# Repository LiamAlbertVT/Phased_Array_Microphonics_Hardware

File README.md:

## Recent Updates

- Corrected the 48 V phantom-power wiring on all four XLR microphone inputs and added a filter before each delay chip.
- Reduced open PCB connections from 64 to 11. All 11 are in the power section.

## TODO (Upcoming Commits)

- Review the Q6 gate drive and the pin assignments on regulators U16 and U18 before finishing the power routing.

## Future Plans

- Test the Raspberry Pi Pico's delay clocks and its connection to the ADC.
  - Add Pico sample code in an `embedded/` directory.
- Build one microphone channel on a breadboard and check its gain, filter response, and delay before ordering the PCB.

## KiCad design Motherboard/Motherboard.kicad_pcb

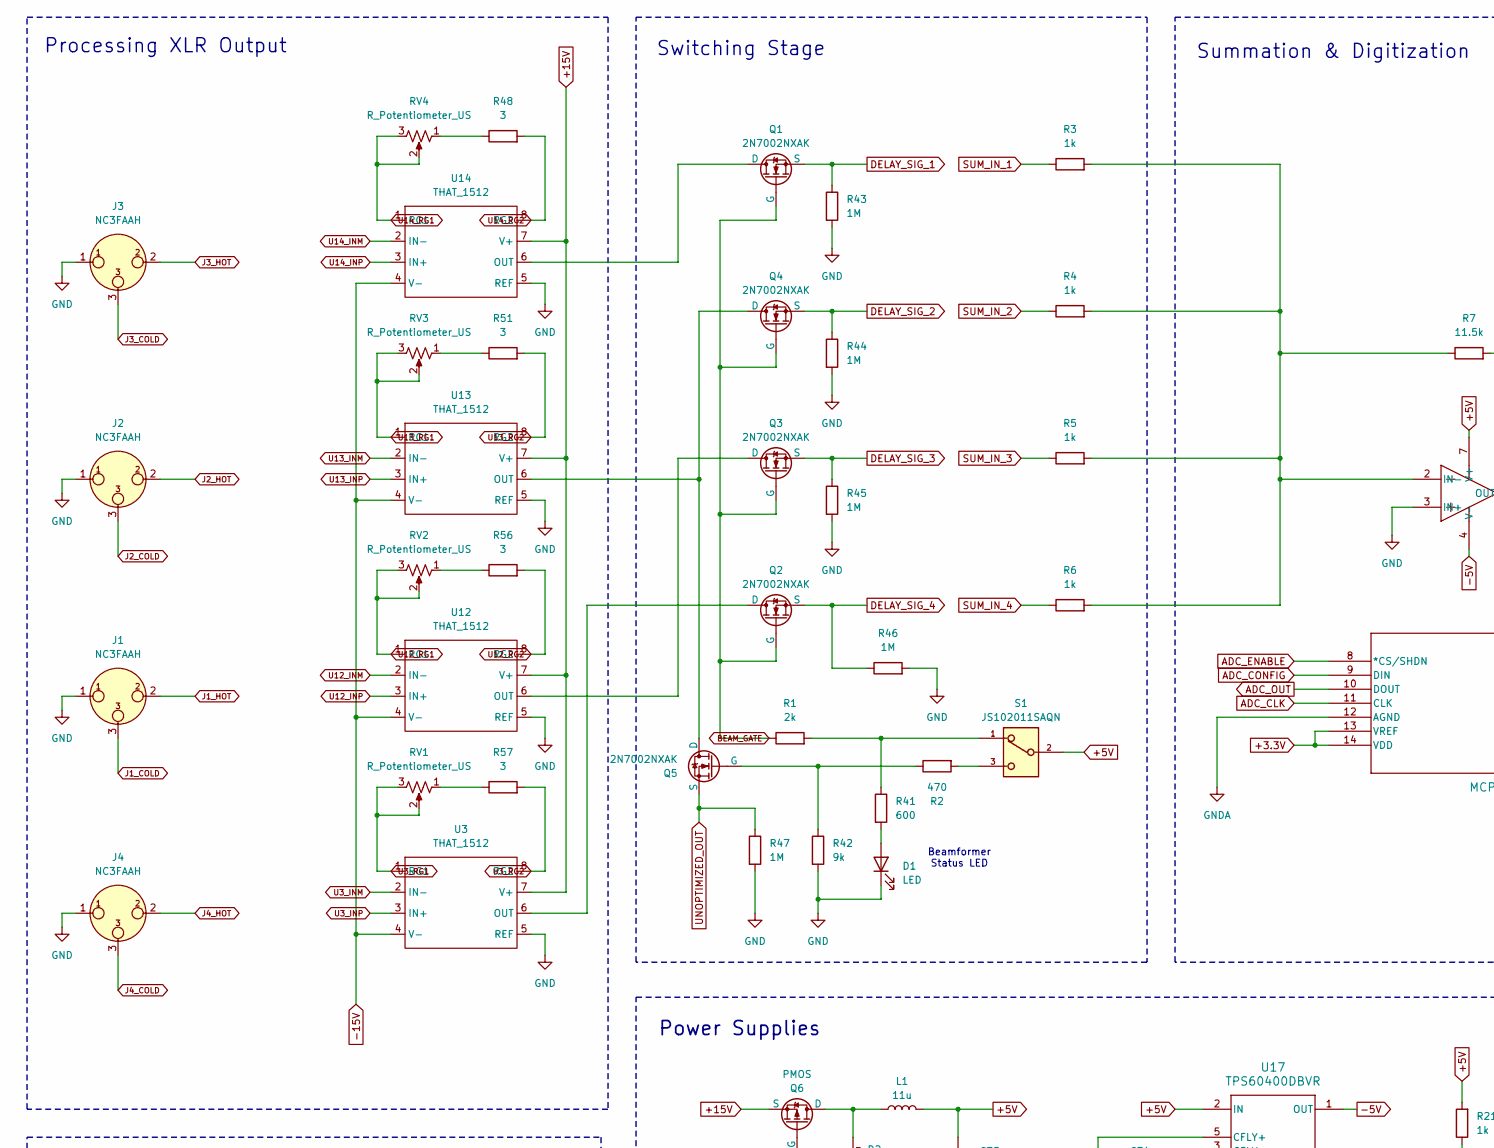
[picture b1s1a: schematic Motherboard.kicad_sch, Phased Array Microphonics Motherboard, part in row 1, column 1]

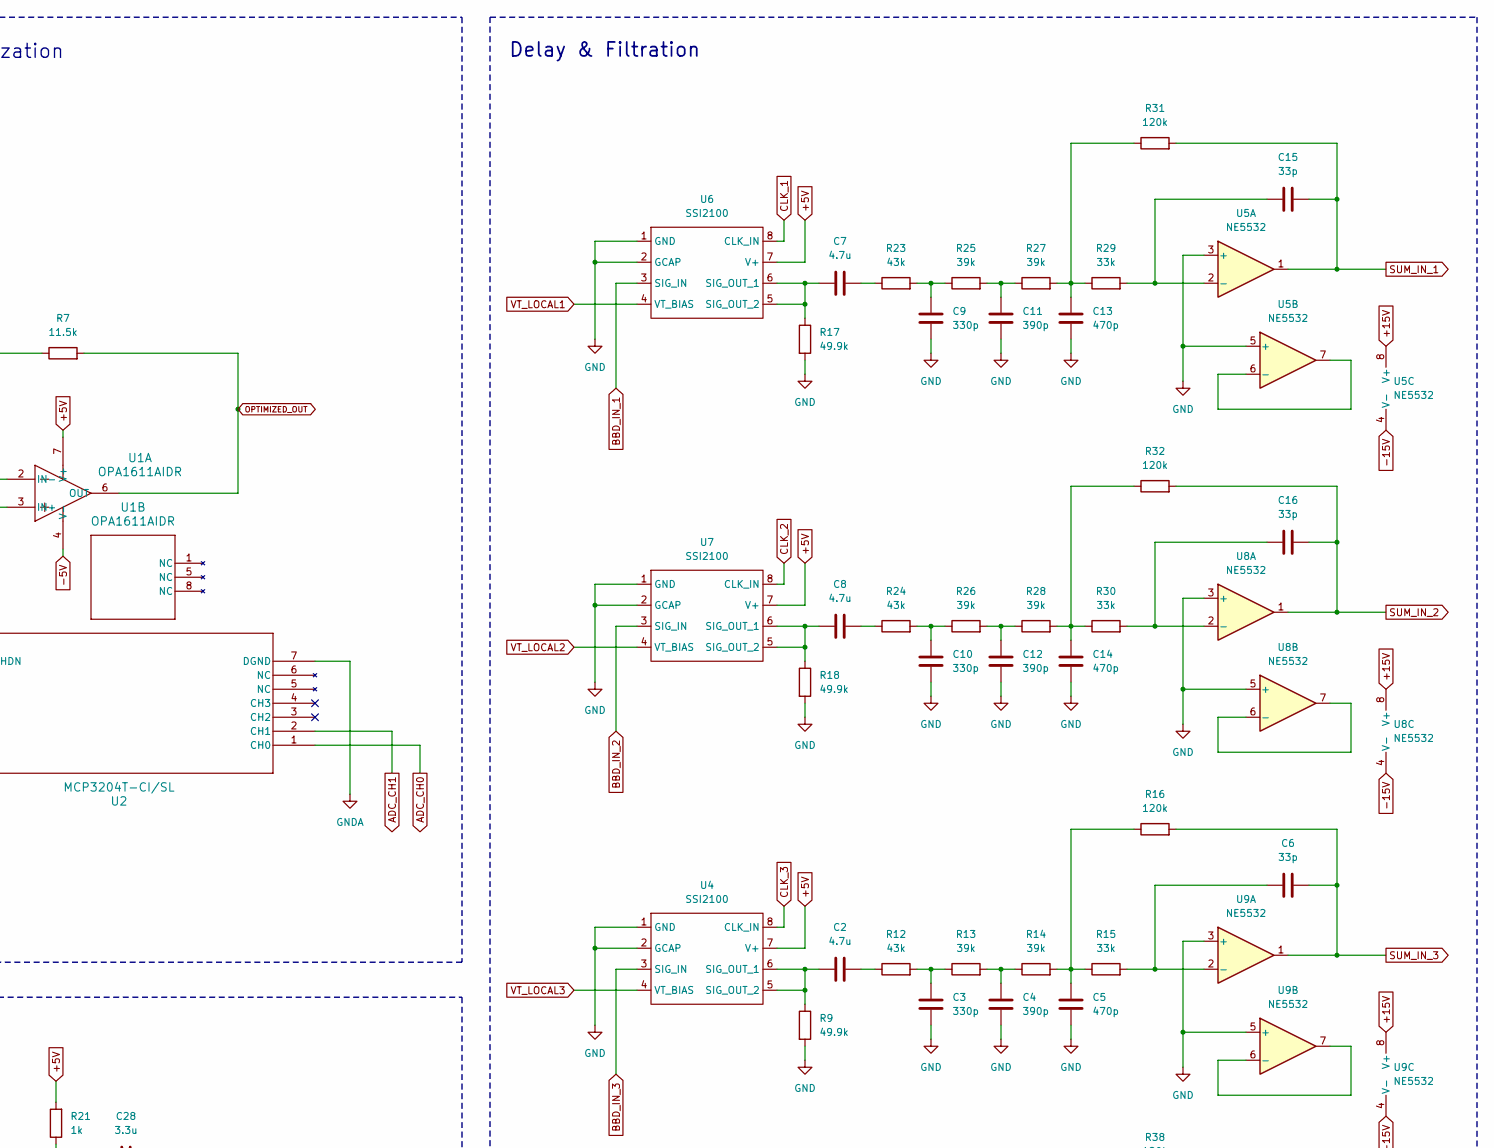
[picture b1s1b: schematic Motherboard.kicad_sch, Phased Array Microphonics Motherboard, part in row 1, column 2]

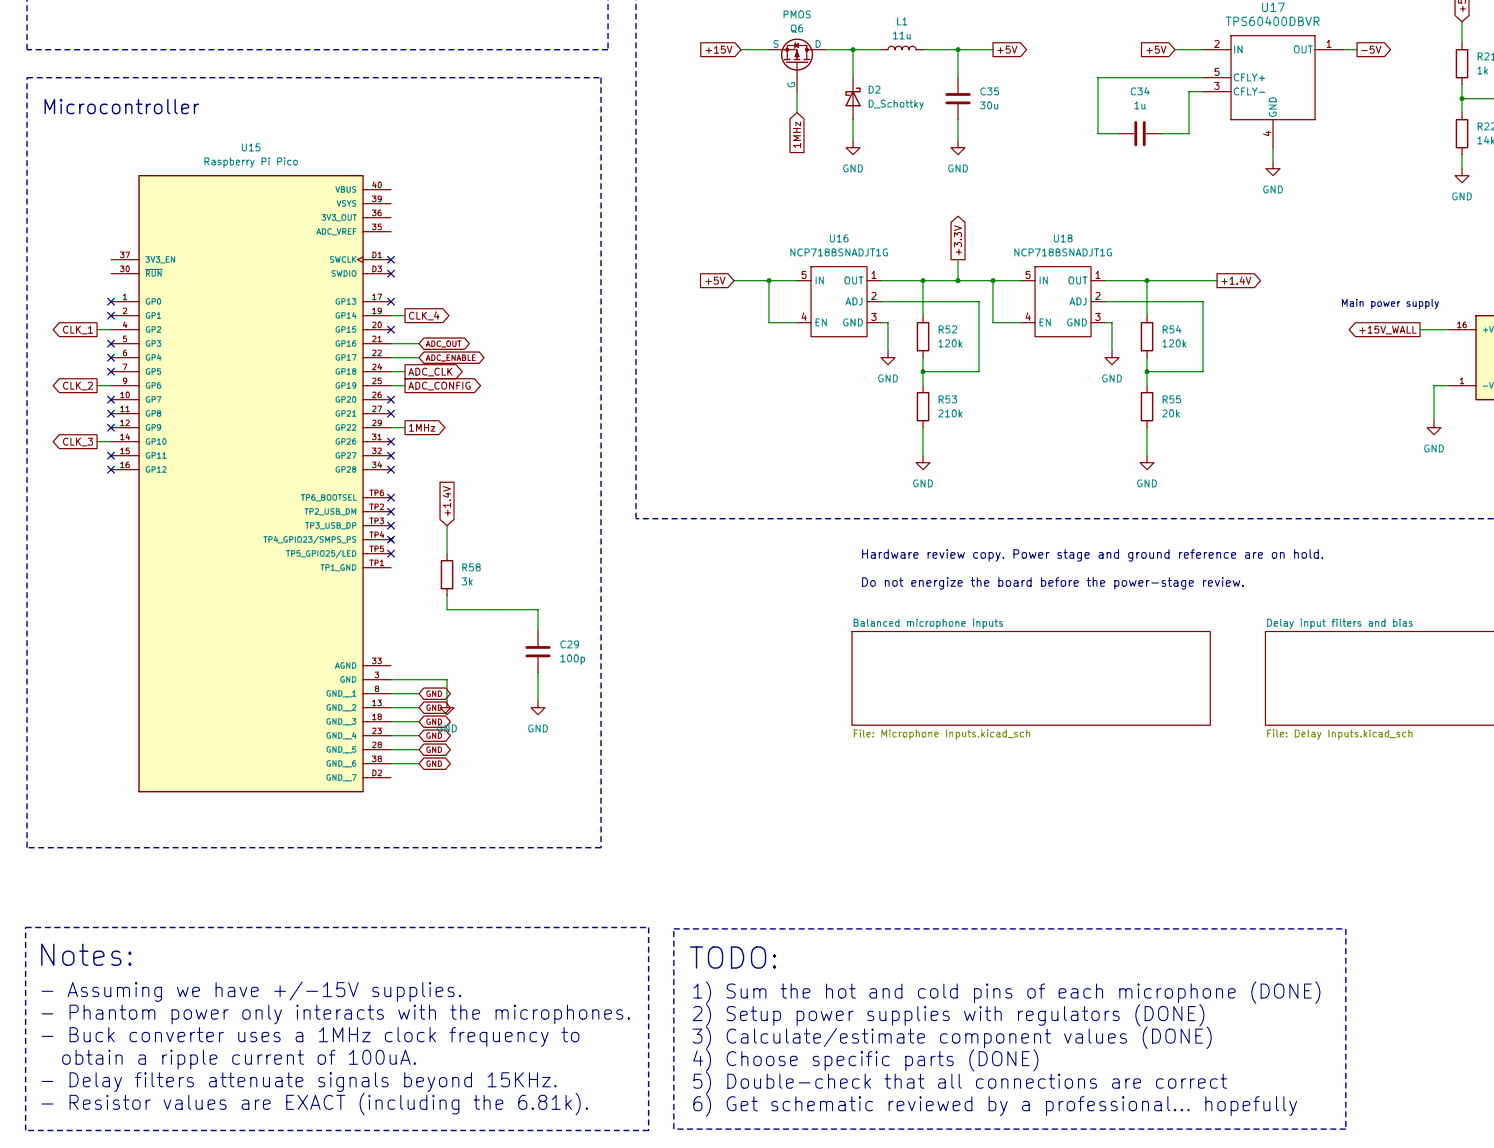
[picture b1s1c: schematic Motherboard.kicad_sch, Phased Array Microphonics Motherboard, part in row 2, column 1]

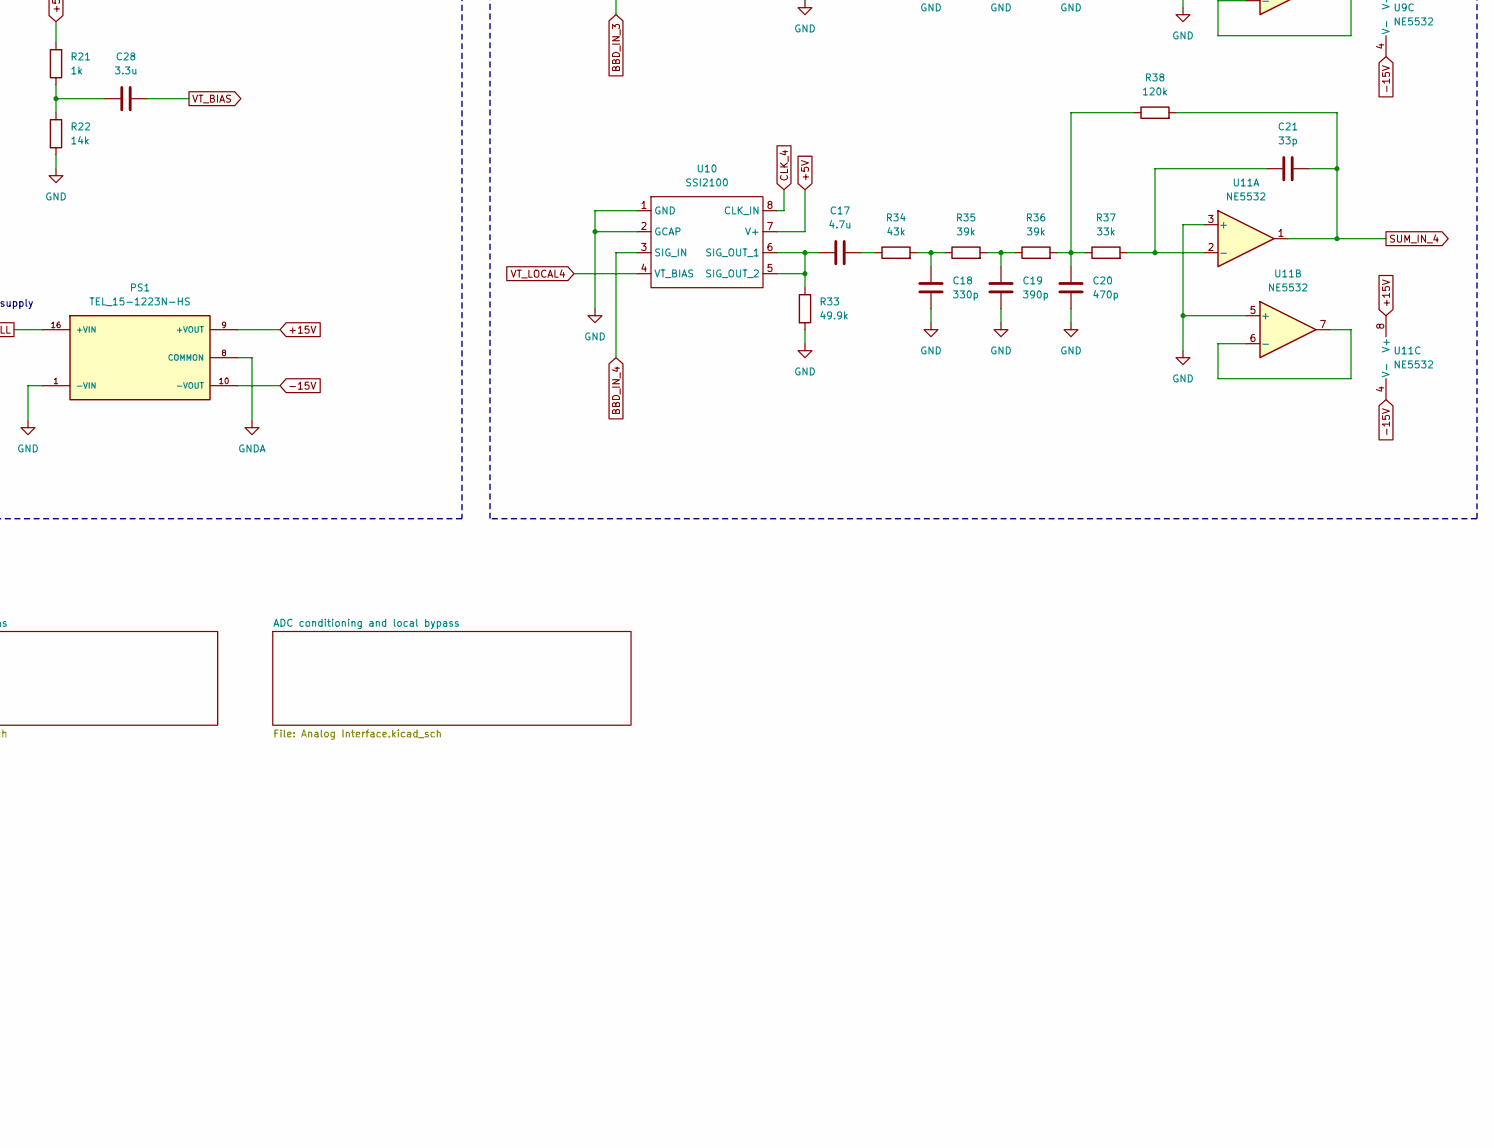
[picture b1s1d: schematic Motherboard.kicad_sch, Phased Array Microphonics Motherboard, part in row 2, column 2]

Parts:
C2, C7, C8, C17: 4.7u; C_0603_1608Metric
C3, C9, C10, C18: 330p; C_0603_1608Metric
C4, C11, C12, C19: 390p; C_0603_1608Metric
C5, C13, C14, C20: 470p; C_0603_1608Metric
C6, C15, C16, C21: 33p; C_0603_1608Metric
C28: 3.3u; C_0603_1608Metric
C29: 100p; C_0805_2012Metric
C34: 1u; C_0603_1608Metric
C35: 30u; C_0805_2012Metric
D1: LED; LTST-C170GKT
D2: D_Schottky; D_SOD-323
J1, J2, J3, J4: NC3FAAH; Jack_XLR_Neutrik_NC3FAAH_Horizontal
L1: 11u; L_APV_APH1265
PS1: TEL_15-1223N-HS; PARTREV November 2, 2022
Q1, Q2, Q3, Q4, Q5: 2N7002NXAK; 2N7002NXAKR
Q6: PMOS; 2N7002NXAKR
R1: 2k; R_0603_1608Metric
R2: 470; R_0603_1608Metric
R3, R4, R5, R6, R21: 1k; R_0603_1608Metric
R7: 11.5k; R_0603_1608Metric
R9, R17, R18, R33: 49.9k; R_0603_1608Metric
R12, R23, R24, R34: 43k; R_0603_1608Metric
R13, R14, R25, R26, R27, R28, R35, R36: 39k; R_0603_1608Metric
R15, R29, R30, R37: 33k; R_0603_1608Metric
R16, R31, R32, R38, R52, R54: 120k; R_0603_1608Metric
R22: 14k; R_0603_1608Metric
R41: 600; R_0603_1608Metric
R42: 9k; R_0603_1608Metric
R43, R44, R45, R46, R47: 1M; R_0603_1608Metric
R48, R51, R56, R57: 3; R_0603_1608Metric
R53: 210k; R_0603_1608Metric
R55: 20k; R_0603_1608Metric
R58: 3k; R_0603_1608Metric
RV1, RV2, RV3, RV4: R_Potentiometer_US; Adafruit_Panel_Mount_1k_Potentiometer_Linear
S1: JS102011SAQN; SW_JS102011SAQN
U1: OPA1611AIDR; SOIC-8_3.9x4.9mm_P1.27mm
U2: MCP3204T-CI/SL; MCP3204T_CI_SL
U3, U12, U13, U14: THAT_1512; SOIC-8_3.9x4.9mm_P1.27mm
U4, U6, U7, U10: SSI2100; SOIC-8_3.9x4.9mm_P1.27mm
U5, U8, U9, U11: NE5532; SOIC-8_3.9x4.9mm_P1.27mm
U15: Raspberry Pi Pico; RaspberryPi_Pico_SMD; PARTREV 1.9
U16, U18: NCP718BSNADJT1G
U17: TPS60400DBVR

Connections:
1MHz: Q6.2 (G), U15.29 (GP22)
+1.4V: R54.1, R58.1, U18.1 (OUT)
+3.3V: R52.1, U2.13 (VREF), U2.14 (VDD), U16.1 (OUT), U18.4 (EN), U18.5 (IN); also elsewhere on the board
+5V: C35.1, L1.2, R21.2, S1.2, U1.7 (V+), U4.7 (V+), U6.7 (V+), U7.7 (V+), U10.7 (V+), U16.4 (EN), U16.5 (IN), U17.2 (IN); also elsewhere on the board
+15V: PS1.9 (+VOUT), Q6.3 (S), U3.7 (V+), U5.8 (V+), U8.8 (V+), U9.8 (V+), U11.8 (V+), U12.7 (V+), U13.7 (V+), U14.7 (V+); also elsewhere on the board
+15V_WALL: PS1.16 (+VIN)
-5V: U1.4 (V-), U17.1 (OUT); also elsewhere on the board
-15V: PS1.10 (-VOUT), U3.4 (V-), U5.4 (V-), U8.4 (V-), U9.4 (V-), U11.4 (V-), U12.4 (V-), U13.4 (V-), U14.4 (V-); also elsewhere on the board
ADC_CH0: U2.1 (CH0); also elsewhere on the board
ADC_CH1: U2.2 (CH1); also elsewhere on the board
ADC_CLK: U2.11 (CLK), U15.24 (GP18)
ADC_CONFIG: U2.9 (DIN), U15.25 (GP19)
ADC_ENABLE: U2.8 (*CS/SHDN), U15.22 (GP17)
ADC_OUT: U2.10 (DOUT), U15.21 (GP16)
BBD_IN_1: U6.3 (SIG_IN); also elsewhere on the board
BBD_IN_2: U7.3 (SIG_IN); also elsewhere on the board
BBD_IN_3: U4.3 (SIG_IN); also elsewhere on the board
BBD_IN_4: U10.3 (SIG_IN); also elsewhere on the board
BEAM_GATE: Q1.1 (G), Q2.1 (G), Q3.1 (G), Q4.1 (G), R1.1; also elsewhere on the board
CLK_1: U6.8 (CLK_IN), U15.4 (GP2)
CLK_2: U7.8 (CLK_IN), U15.9 (GP6)
CLK_3: U4.8 (CLK_IN), U15.14 (GP10)
CLK_4: U10.8 (CLK_IN), U15.19 (GP14)
DELAY_SIG_1: Q1.2 (S), R43.1; also elsewhere on the board
DELAY_SIG_2: Q4.2 (S), R44.1; also elsewhere on the board
DELAY_SIG_3: Q3.2 (S), R45.1; also elsewhere on the board
DELAY_SIG_4: Q2.2 (S), R46.1; also elsewhere on the board
GND: C3.1, C4.1, C5.1, C9.1, C10.1, C11.1, C12.1, C13.1, C14.1, C18.1, C19.1, C20.1, C29.2, C35.2, D1.1 (K), D2.2 (A), J1.1, J2.1, J3.1, J4.1, PS1.1 (-VIN), R9.2, R17.2, R18.2, R22.2, R33.2, R42.2, R43.2, R44.2, R45.2, R46.2, R47.2, R53.2, R55.2, U1.3 (IN+), U3.5 (REF), U4.1 (GND), U4.2 (GCAP), U5.3 (+), U5.5 (+), U6.1 (GND), U6.2 (GCAP), U7.1 (GND), U7.2 (GCAP), U8.3 (+), U8.5 (+), U9.3 (+), U9.5 (+), U10.1 (GND), U10.2 (GCAP), U11.3 (+), U11.5 (+), U12.5 (REF), U13.5 (REF), U14.5 (REF), U15.3 (GND), U15.8 (GND__1), U15.13 (GND__2), U15.18 (GND__3), U15.23 (GND__4), U15.28 (GND__5), U15.38 (GND__6), U16.3 (GND), U17.4 (GND), U18.3 (GND); also elsewhere on the board
GNDA: PS1.8 (COMMON), U2.7 (DGND), U2.12 (AGND); also elsewhere on the board
J1_COLD: J1.3; also elsewhere on the board
J1_HOT: J1.2; also elsewhere on the board
J2_COLD: J2.3; also elsewhere on the board
J2_HOT: J2.2; also elsewhere on the board
J3_COLD: J3.3; also elsewhere on the board
J3_HOT: J3.2; also elsewhere on the board
J4_COLD: J4.3; also elsewhere on the board
J4_HOT: J4.2; also elsewhere on the board
unnamed: C2.2, R12.1
unnamed: C3.2, R12.2, R13.1
unnamed: C4.2, R13.2, R14.1
unnamed: C5.2, R14.2, R15.1, R16.1
unnamed: C7.2, R23.1
unnamed: C8.2, R24.1
unnamed: C9.2, R23.2, R25.1
unnamed: C10.2, R24.2, R26.1
unnamed: C11.2, R25.2, R27.1
unnamed: C12.2, R26.2, R28.1
unnamed: C13.2, R27.2, R29.1, R31.1
unnamed: C14.2, R28.2, R30.1, R32.1
unnamed: C17.2, R34.1
unnamed: C18.2, R34.2, R35.1
unnamed: C19.2, R35.2, R36.1
unnamed: C20.2, R36.2, R37.1, R38.1
unnamed: C28.1, R21.1, R22.1
unnamed: C29.1, R58.2
unnamed: D1.2 (A), R41.2
unnamed: D2.1 (K), L1.1, Q6.1 (D)
unnamed: Q1.3 (D), U14.6 (OUT)
unnamed: Q2.3 (D), U3.6 (OUT)
unnamed: Q3.3 (D), U12.6 (OUT)
unnamed: Q4.3 (D), Q5.3 (D), U13.6 (OUT)
unnamed: Q5.1 (G), R2.1, R42.1
unnamed: R1.2, R41.1, S1.1
unnamed: R2.2, S1.3
unnamed: R48.1, RV4.1
unnamed: R51.1, RV3.1
unnamed: R56.1, RV2.1
unnamed: R57.1, RV1.1
unnamed: R3.2, R4.2, R5.2, R6.2, R7.1, U1.2 (IN-)
unnamed: C2.1, R9.1, U4.5 (SIG_OUT_2), U4.6 (SIG_OUT_1)
unnamed: C15.2, R29.2, U5.2 (-)
unnamed: U5.6 (-), U5.7
unnamed: C7.1, R17.1, U6.5 (SIG_OUT_2), U6.6 (SIG_OUT_1)
unnamed: C8.1, R18.1, U7.5 (SIG_OUT_2), U7.6 (SIG_OUT_1)
unnamed: C16.2, R30.2, U8.2 (-)
unnamed: U8.6 (-), U8.7
unnamed: C6.2, R15.2, U9.2 (-)
unnamed: U9.6 (-), U9.7
unnamed: C17.1, R33.1, U10.5 (SIG_OUT_2), U10.6 (SIG_OUT_1)
unnamed: C21.2, R37.2, U11.2 (-)
unnamed: U11.6 (-), U11.7
unnamed: R52.2, R53.1, U16.2 (ADJ)
unnamed: C34.2, U17.5 (CFLY+)
unnamed: C34.1, U17.3 (CFLY-)
unnamed: R54.2, R55.1, U18.2 (ADJ)
OPTIMIZED_OUT: R7.2, U1.6 (OUT); also elsewhere on the board
SUM_IN_1: C15.1, R3.1, R31.2, U5.1
SUM_IN_2: C16.1, R4.1, R32.2, U8.1
SUM_IN_3: C6.1, R5.1, R16.2, U9.1
SUM_IN_4: C21.1, R6.1, R38.2, U11.1
U3_INM: U3.2 (IN-); also elsewhere on the board
U3_INP: U3.3 (IN+); also elsewhere on the board
U3_RG1: RV1.2, RV1.3, U3.1 (RG1); also elsewhere on the board
U3_RG2: R57.2, U3.8 (RG2); also elsewhere on the board
U12_INM: U12.2 (IN-); also elsewhere on the board
U12_INP: U12.3 (IN+); also elsewhere on the board
U12_RG1: RV2.2, RV2.3, U12.1 (RG1); also elsewhere on the board
U12_RG2: R56.2, U12.8 (RG2); also elsewhere on the board
U13_INM: U13.2 (IN-); also elsewhere on the board
U13_INP: U13.3 (IN+); also elsewhere on the board
U13_RG1: RV3.2, RV3.3, U13.1 (RG1); also elsewhere on the board
U13_RG2: R51.2, U13.8 (RG2); also elsewhere on the board
U14_INM: U14.2 (IN-); also elsewhere on the board
U14_INP: U14.3 (IN+); also elsewhere on the board
U14_RG1: RV4.2, RV4.3, U14.1 (RG1); also elsewhere on the board
U14_RG2: R48.2, U14.8 (RG2); also elsewhere on the board
UNOPTIMIZED_OUT: Q5.2 (S), R47.1; also elsewhere on the board
VT_BIAS: C28.2
VT_LOCAL1: U6.4 (VT_BIAS); also elsewhere on the board
VT_LOCAL2: U7.4 (VT_BIAS); also elsewhere on the board
VT_LOCAL3: U4.4 (VT_BIAS); also elsewhere on the board
VT_LOCAL4: U10.4 (VT_BIAS); also elsewhere on the board

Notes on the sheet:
Summation & Digitization
Switching Stage
Delay & Filtration
Beamformer Status LED
1) Sum the hot and cold pins of each microphone (DONE) 2) Setup power supplies with regulators (DONE) 3) Calculate/estimate component values (DONE) 4) Choose specific parts (DONE) 5) Double-check that all connections are correct 6) Get schematic reviewed by a professional... hopefully
TODO:
- Assuming we have +/-15V supplies. - Phantom power only interacts with the microphones. - Buck converter uses a 1MHz clock frequency to obtain a ripple current of 100uA. - Delay filters attenuate signals beyond 15KHz. - Resistor values are EXACT (including the 6.81k).
Power Supplies
Processing XLR Output
Notes:
Main power supply
Microcontroller
Hardware review copy. Power stage and ground reference are on hold.
Do not energize the board before the power-stage review.

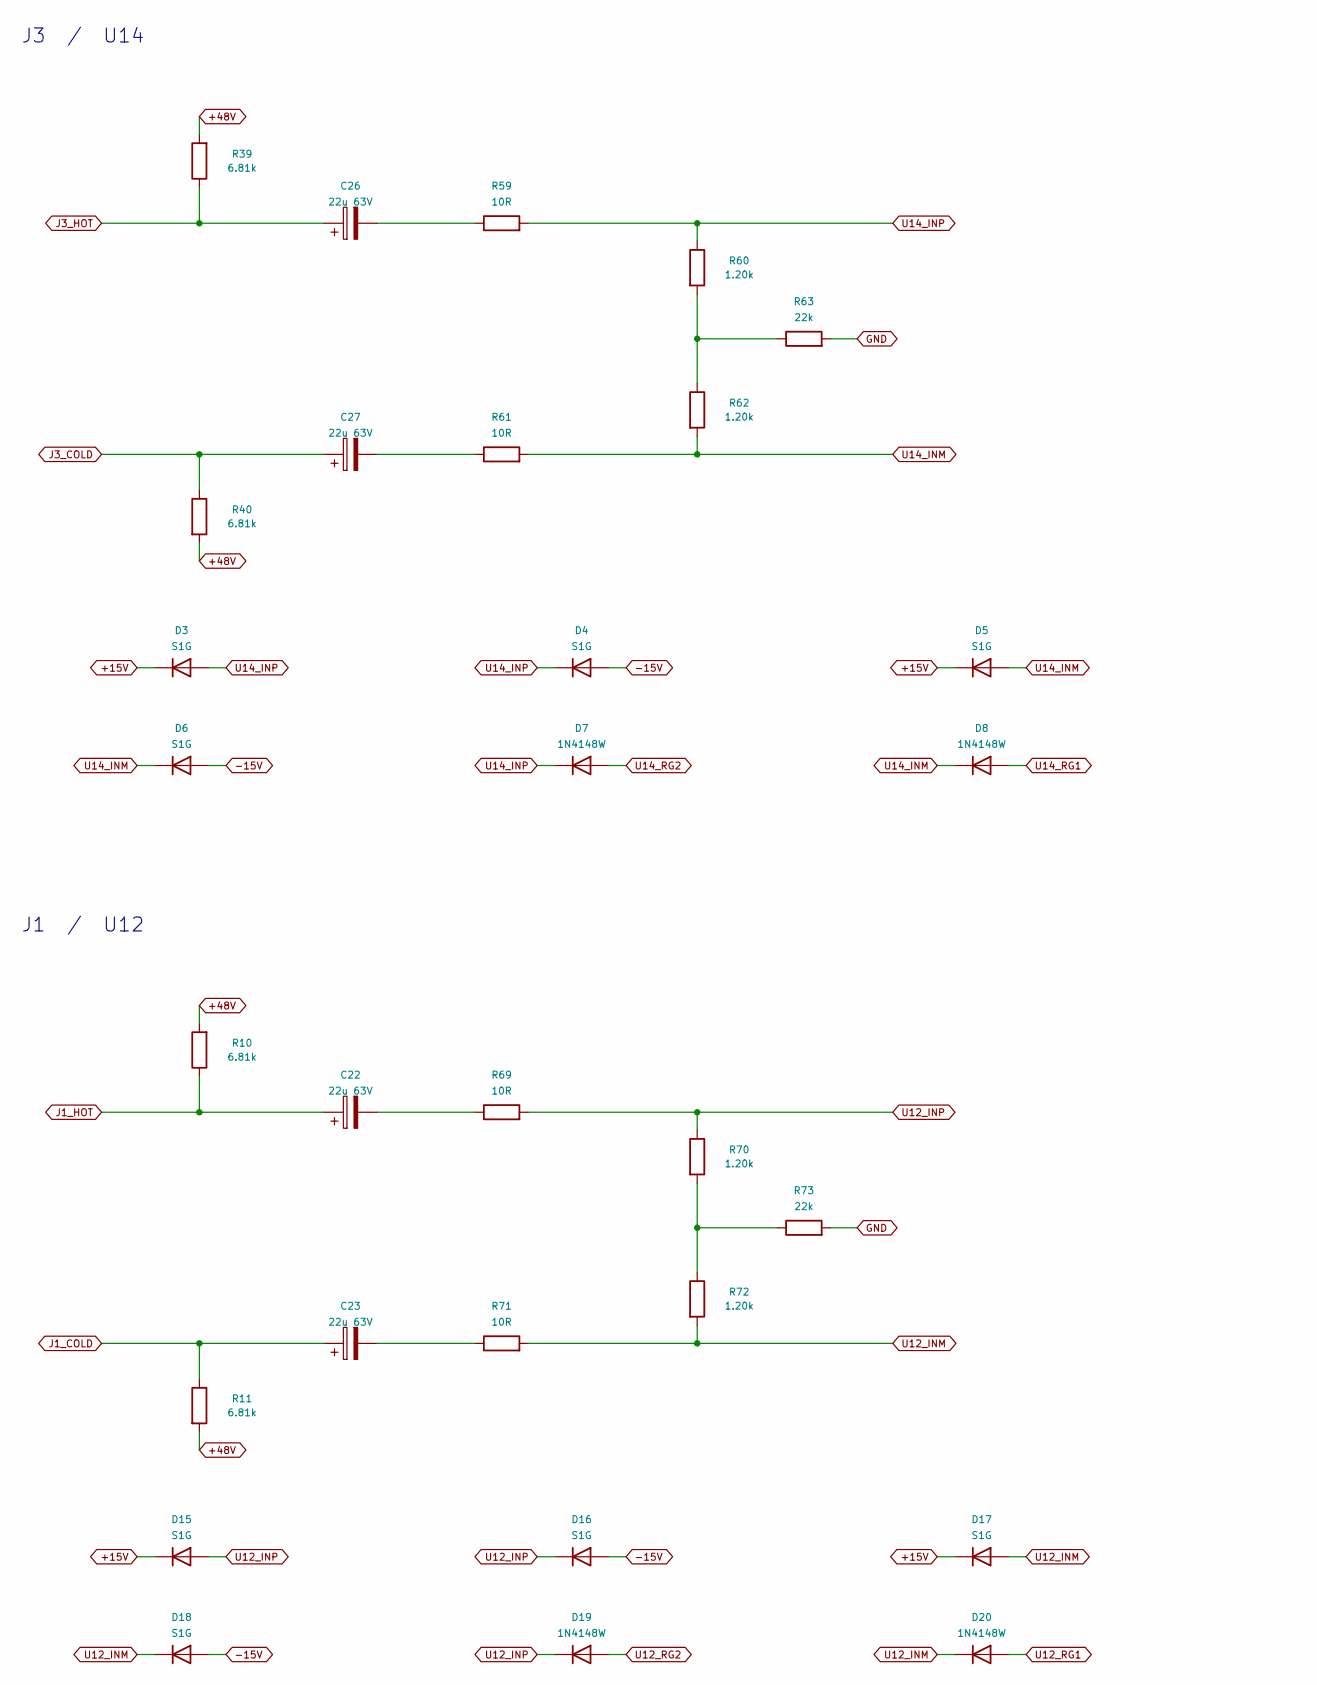
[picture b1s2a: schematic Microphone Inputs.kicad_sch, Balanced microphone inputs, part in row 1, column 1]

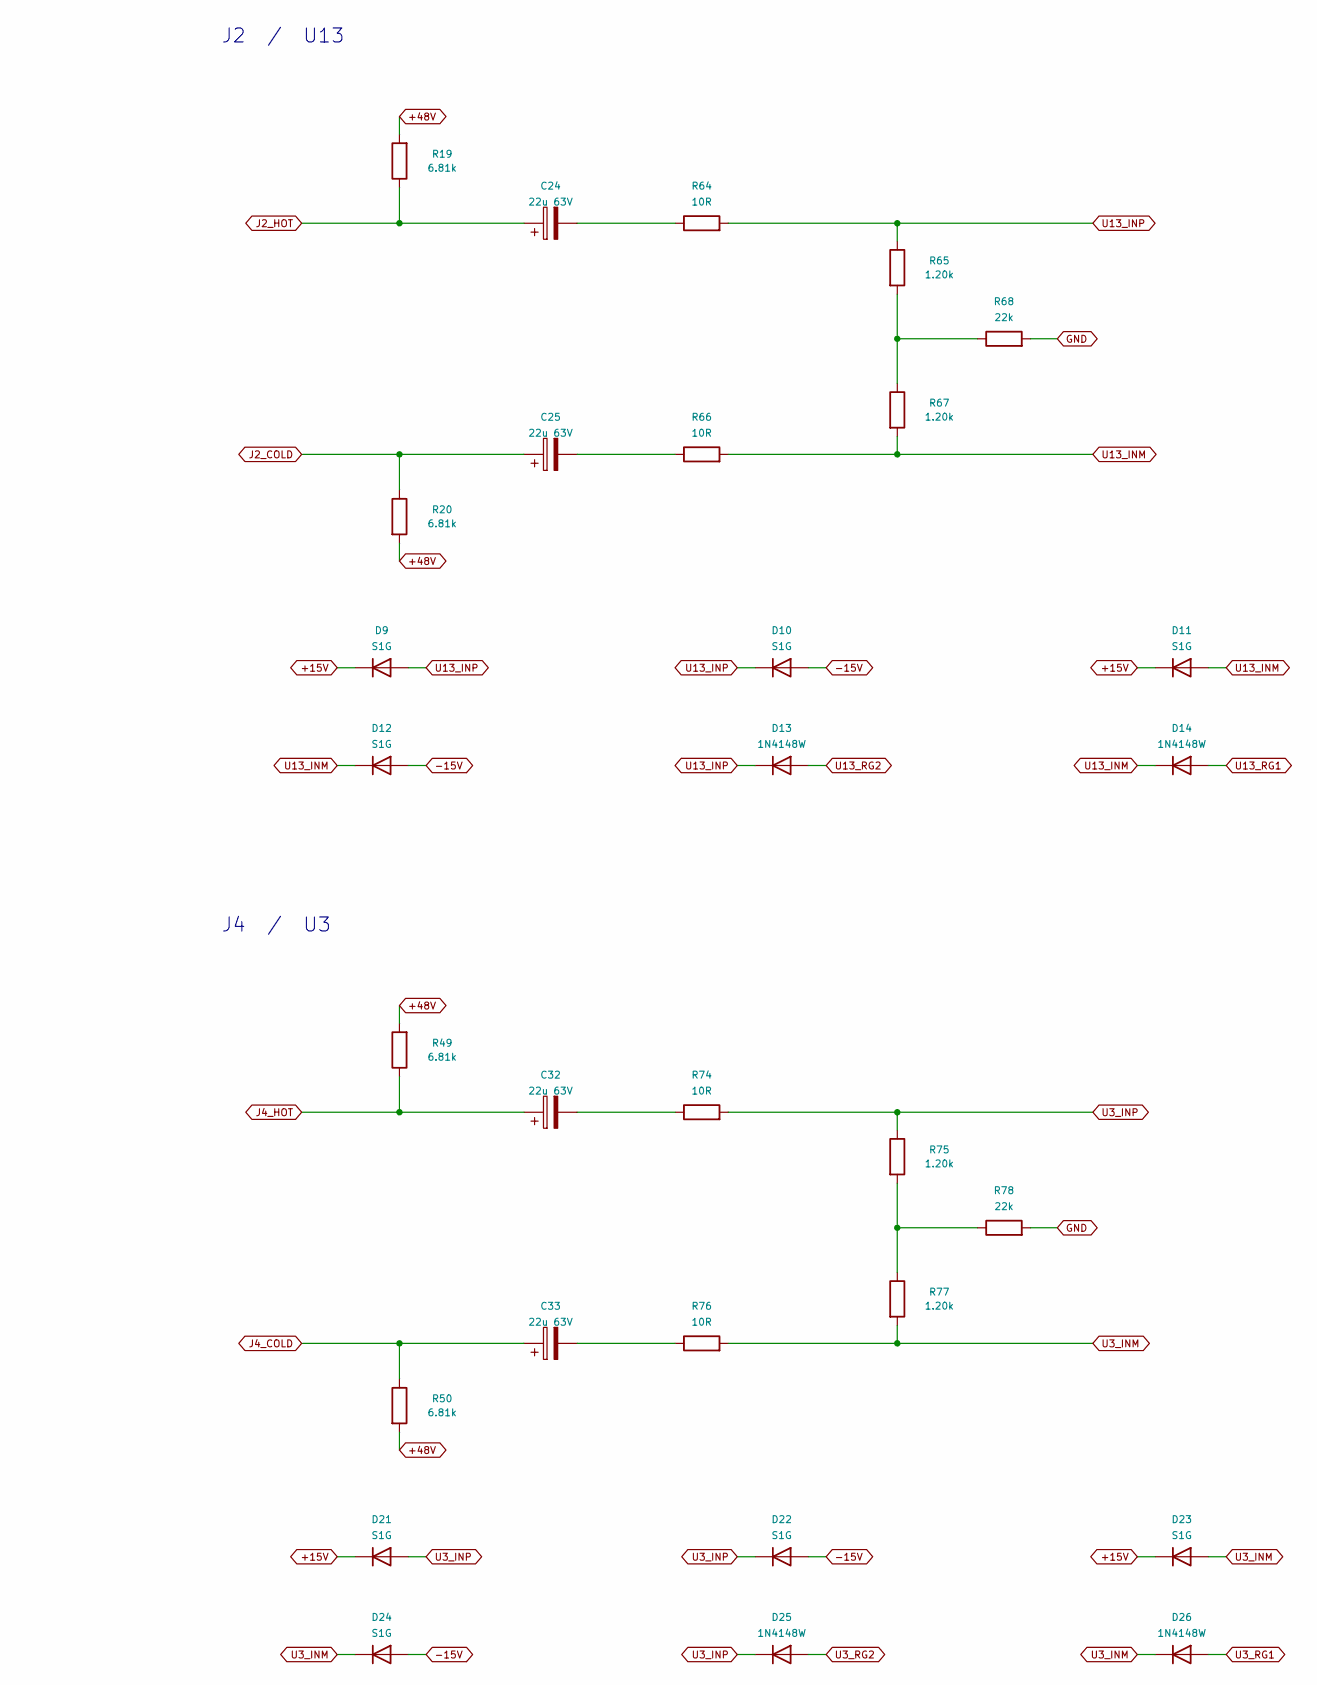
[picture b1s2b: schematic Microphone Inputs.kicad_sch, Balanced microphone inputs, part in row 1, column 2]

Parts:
C22, C23, C24, C25, C26, C27, C32, C33: 22u 63V; CP_Radial_D6.3mm_P2.50mm; Rating 63 V minimum. Positive lead to XLR.
D3, D4, D5, D6, D9, D10, D11, D12, D15, D16, D17, D18, D21, D22, D23, D24: S1G; D_SMA
D7, D8, D13, D14, D19, D20, D25, D26: 1N4148W; D_SOD-123
R10, R11, R19, R20, R39, R40, R49, R50: 6.81k; R_2512_6332Metric; Rating 1 W, 0.1%, pair matched.
R59, R61, R64, R66, R69, R71, R74, R76: 10R; R_1206_3216Metric; Rating Pulse-rated, matched pair.
R60, R62, R65, R67, R70, R72, R75, R77: 1.20k; R_0603_1608Metric
R63, R68, R73, R78: 22k; R_0603_1608Metric

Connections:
+15V: D3.1 (K), D5.1 (K), D9.1 (K), D11.1 (K), D15.1 (K), D17.1 (K), D21.1 (K), D23.1 (K); also elsewhere on the board
+48V: R10.2, R11.2, R19.2, R20.2, R39.2, R40.2, R49.2, R50.2
-15V: D4.2 (A), D6.2 (A), D10.2 (A), D12.2 (A), D16.2 (A), D18.2 (A), D22.2 (A), D24.2 (A); also elsewhere on the board
GND: R63.2, R68.2, R73.2, R78.2; also elsewhere on the board
J1_COLD: C23.1, R11.1; also elsewhere on the board
J1_HOT: C22.1, R10.1; also elsewhere on the board
J2_COLD: C25.1, R20.1; also elsewhere on the board
J2_HOT: C24.1, R19.1; also elsewhere on the board
J3_COLD: C27.1, R40.1; also elsewhere on the board
J3_HOT: C26.1, R39.1; also elsewhere on the board
J4_COLD: C33.1, R50.1; also elsewhere on the board
J4_HOT: C32.1, R49.1; also elsewhere on the board
unnamed: C22.2, R69.1
unnamed: C23.2, R71.1
unnamed: C24.2, R64.1
unnamed: C25.2, R66.1
unnamed: C26.2, R59.1
unnamed: C27.2, R61.1
unnamed: C32.2, R74.1
unnamed: C33.2, R76.1
unnamed: R60.2, R62.1, R63.1
unnamed: R65.2, R67.1, R68.1
unnamed: R70.2, R72.1, R73.1
unnamed: R75.2, R77.1, R78.1
U3_INM: D23.2 (A), D24.1 (K), D26.1 (K), R76.2, R77.2; also elsewhere on the board
U3_INP: D21.2 (A), D22.1 (K), D25.1 (K), R74.2, R75.1; also elsewhere on the board
U3_RG1: D26.2 (A); also elsewhere on the board
U3_RG2: D25.2 (A); also elsewhere on the board
U12_INM: D17.2 (A), D18.1 (K), D20.1 (K), R71.2, R72.2; also elsewhere on the board
U12_INP: D15.2 (A), D16.1 (K), D19.1 (K), R69.2, R70.1; also elsewhere on the board
U12_RG1: D20.2 (A); also elsewhere on the board
U12_RG2: D19.2 (A); also elsewhere on the board
U13_INM: D11.2 (A), D12.1 (K), D14.1 (K), R66.2, R67.2; also elsewhere on the board
U13_INP: D9.2 (A), D10.1 (K), D13.1 (K), R64.2, R65.1; also elsewhere on the board
U13_RG1: D14.2 (A); also elsewhere on the board
U13_RG2: D13.2 (A); also elsewhere on the board
U14_INM: D5.2 (A), D6.1 (K), D8.1 (K), R61.2, R62.2; also elsewhere on the board
U14_INP: D3.2 (A), D4.1 (K), D7.1 (K), R59.2, R60.1; also elsewhere on the board
U14_RG1: D8.2 (A); also elsewhere on the board
U14_RG2: D7.2 (A); also elsewhere on the board

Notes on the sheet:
J3 / U14
J2 / U13
J1 / U12
J4 / U3
